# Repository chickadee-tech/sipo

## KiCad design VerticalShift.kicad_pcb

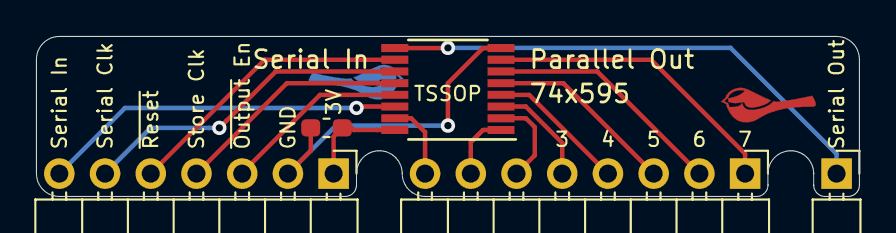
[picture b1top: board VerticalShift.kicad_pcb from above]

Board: 2 copper layers, 45.7 x 8.9 mm, 5 parts (0 on the bottom side), 16 nets.

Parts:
C1: C_Small; C_0603_1608Metric_Pad1.05x0.95mm_HandSolder
J1: Conn_01x07_Male; PinHeader_1x07_P2.54mm_Horizontal
J2: Conn_01x08_Male; PinHeader_1x08_P2.54mm_Horizontal
J3: Conn_01x01_Male; PinHeader_1x01_P2.54mm_Horizontal
U1: 74LS595; TSSOP-16_4.4x5mm_P0.65mm

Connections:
/7: J2.1, U1.7
/RCLK: J1.4, U1.12
/SCLK: J1.6, U1.11
/SER: J1.7, U1.14
/~OE: J1.3, U1.13
/~RST: J1.5, U1.10
GND: C1.2, J1.2, U1.8
unnamed: J2.2, U1.6
unnamed: J2.3, U1.5
unnamed: J2.4, U1.4
unnamed: J2.5, U1.3
unnamed: J2.6, U1.2
unnamed: J2.7, U1.1
unnamed: J2.8, U1.15
unnamed: J3.1, U1.9
VCC: C1.1, J1.1, U1.16
